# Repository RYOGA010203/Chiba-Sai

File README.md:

# Chiba-Sai
ちばサイのスイッチ基板のガーバーファイルです。緑色のCodeからZIP形式でダウンロードし、プリント基板を発注するサイト(Seeed Studio)に直接chibasai.zipをアップロードすればOKです。
ただし、ダウンロードした際にファイル名がChiba-Sai-mainとなっているはずなので、そこからchibasai.zipを取り出す必要があります。
Seeed Studio：https://www.fusionpcb.jp/fusion_pcb.html

chibasai_board のフォルダーには、Eagleで編集可能な基板データ（回路図と基板図）があります。

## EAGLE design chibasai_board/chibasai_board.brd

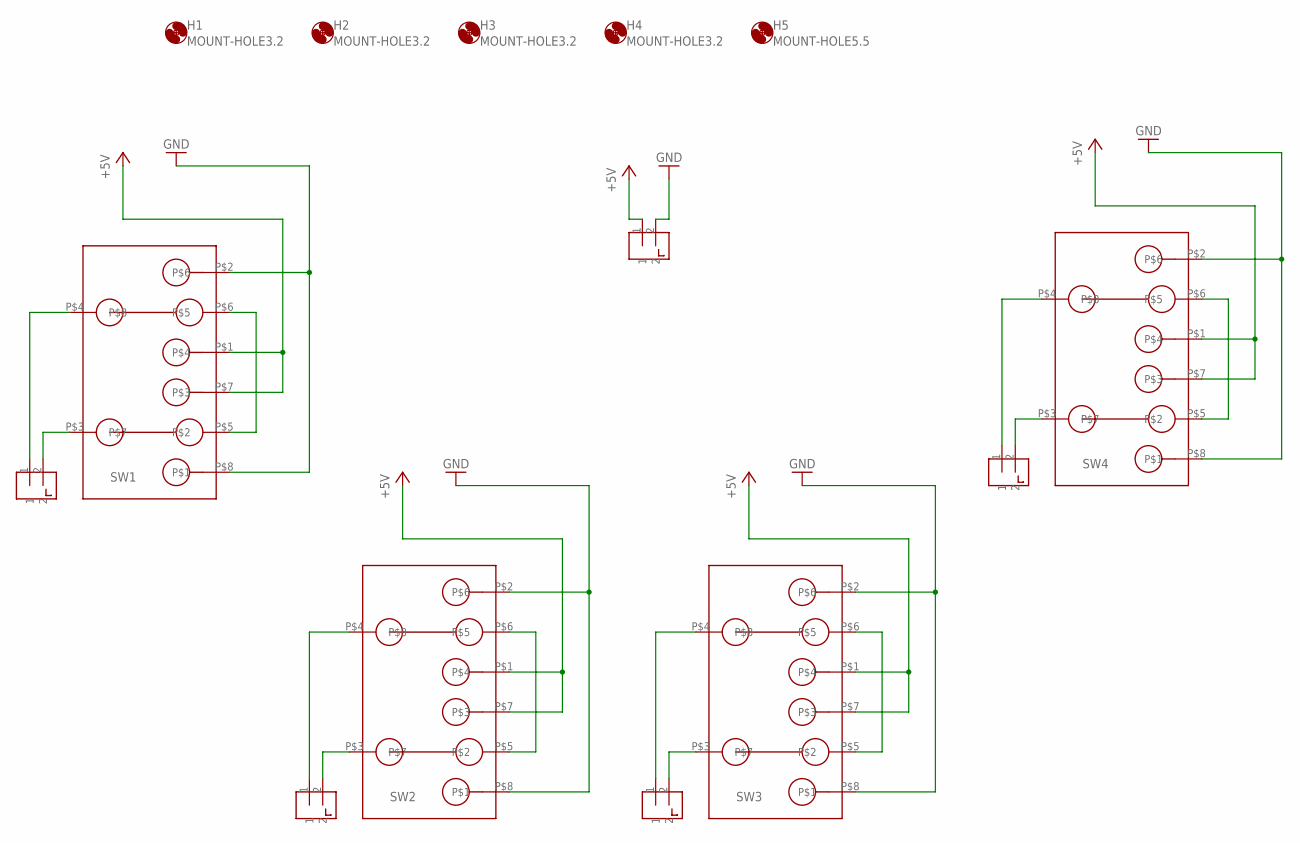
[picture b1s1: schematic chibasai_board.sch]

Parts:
CONNECTOR1, CONNECTOR2, CONNECTOR3, CONNECTOR4, CONNECTOR5: 2PIN
H1, H2, H3, H4: MOUNT-HOLE3.2; 3,2
H5: MOUNT-HOLE5.5; 5,5
SW1, SW2, SW3, SW4: ちばロボのSW; SWのフートプリント

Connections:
+5V: CONNECTOR5.1, SW1.P$1, SW1.P$7, SW2.P$1, SW2.P$7, SW3.P$1, SW3.P$7, SW4.P$1, SW4.P$7
GND: CONNECTOR5.2, SW1.P$2, SW1.P$8, SW2.P$2, SW2.P$8, SW3.P$2, SW3.P$8, SW4.P$2, SW4.P$8
unnamed: SW1.P$5, SW1.P$6
unnamed: SW2.P$5, SW2.P$6
unnamed: SW3.P$5, SW3.P$6
unnamed: SW4.P$5, SW4.P$6
unnamed: CONNECTOR1.1, SW1.P$4
unnamed: CONNECTOR1.2, SW1.P$3
unnamed: CONNECTOR2.1, SW2.P$4
unnamed: CONNECTOR2.2, SW2.P$3
unnamed: CONNECTOR3.1, SW3.P$4
unnamed: CONNECTOR3.2, SW3.P$3
unnamed: CONNECTOR4.1, SW4.P$4
unnamed: CONNECTOR4.2, SW4.P$3

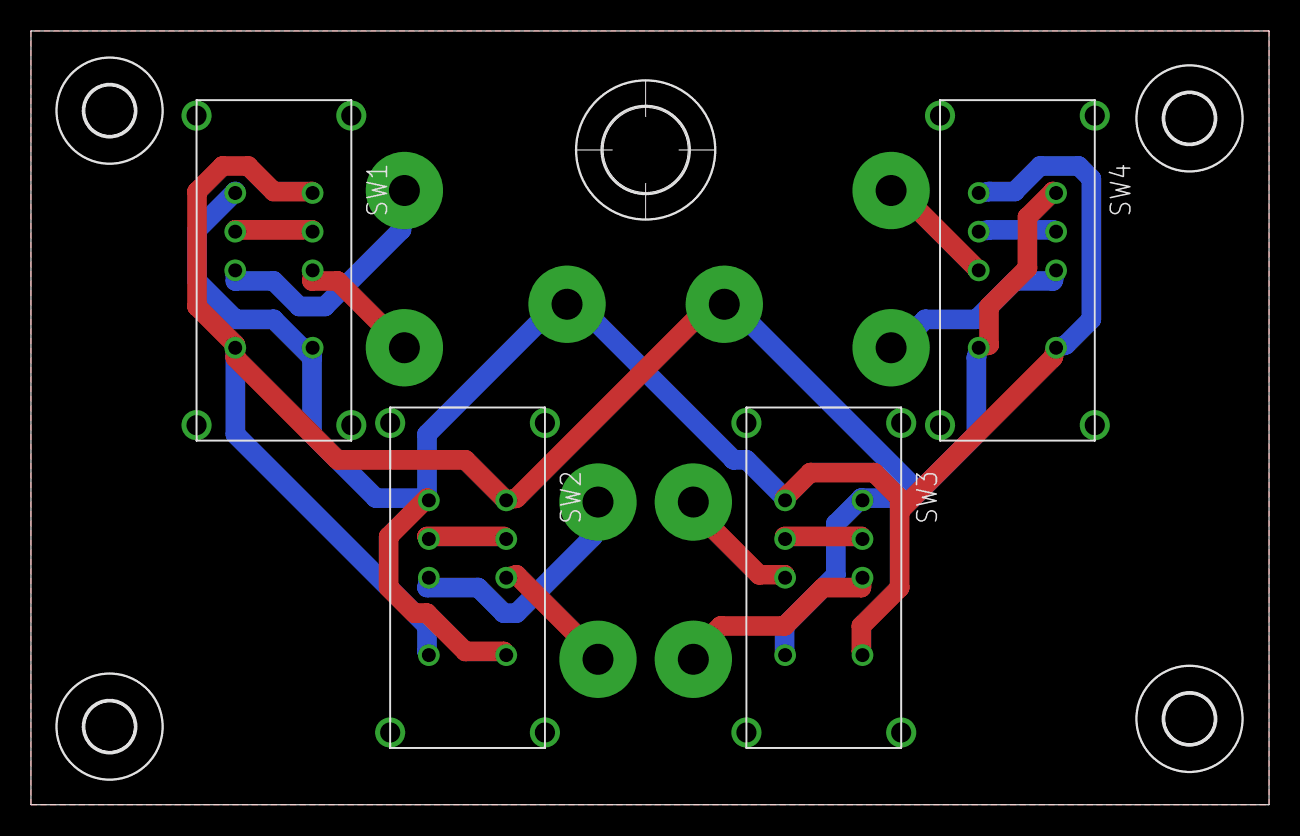
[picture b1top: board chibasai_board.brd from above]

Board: 2 copper layers, 80.0 x 50.0 mm, 14 parts (0 on the bottom side), 14 nets.
